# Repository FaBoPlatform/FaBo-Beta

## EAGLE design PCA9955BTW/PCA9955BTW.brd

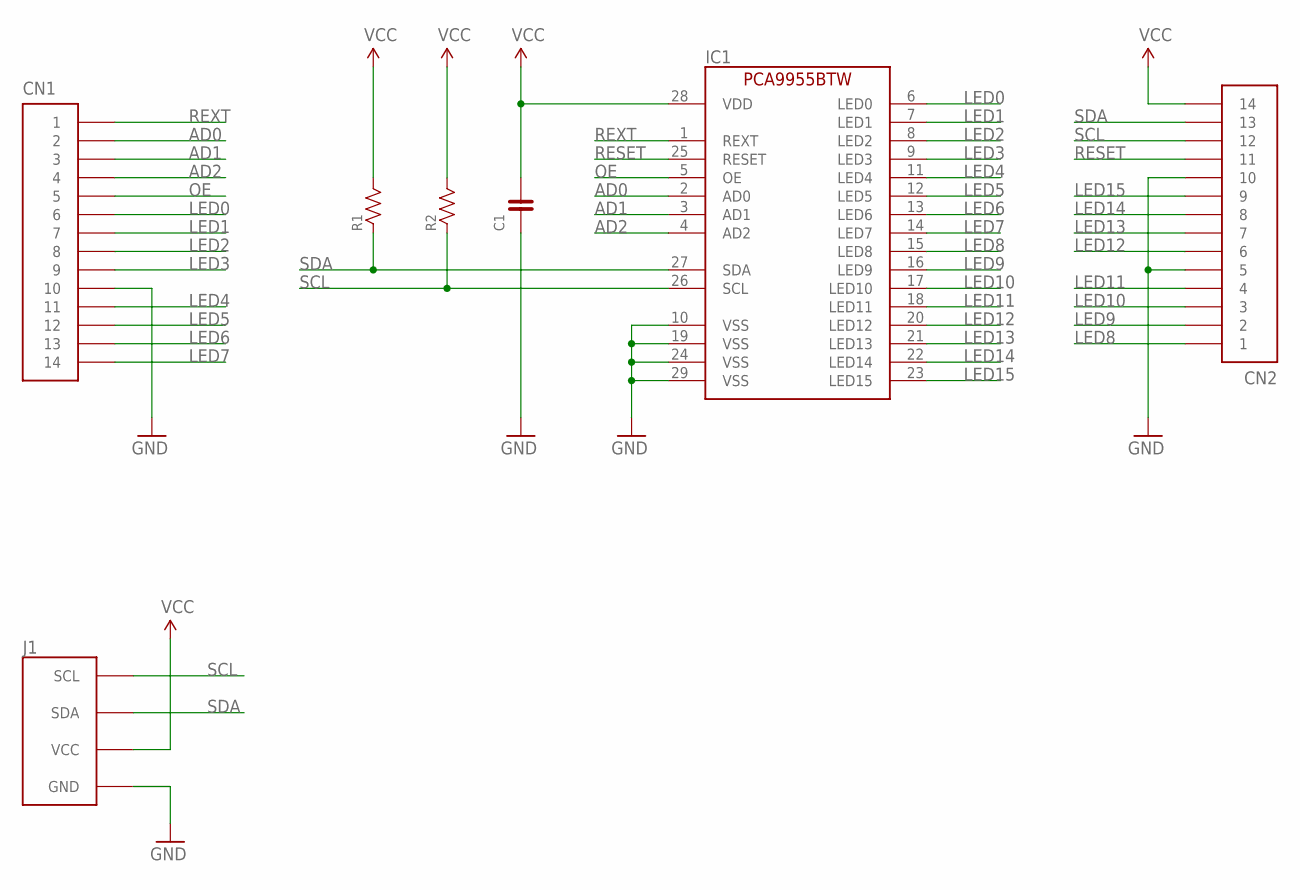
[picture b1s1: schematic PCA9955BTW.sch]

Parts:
C1: CAPACITOR-0603; 0603
CN1, CN2: PIN_HEADER_1X14; PIN_1X14_SNEAKY
IC1: PCA9955BTW; HTSSOP28
J1: FABO_BRICK_I2C-CONNECTOR; FABO_BRICK_I2C_CONNECTOR
R1, R2: RESISTOR-0603; 0603

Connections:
AD0: CN1.2, IC1.2 (AD0)
AD1: CN1.3, IC1.3 (AD1)
AD2: CN1.4, IC1.4 (AD2)
GND: C1.1, CN1.10, CN2.5, CN2.10, IC1.10 (VSS), IC1.19 (VSS), IC1.24 (VSS), IC1.29 (VSS), J1.GND
LED0: CN1.6, IC1.6 (LED0)
LED1: CN1.7, IC1.7 (LED1)
LED2: CN1.8, IC1.8 (LED2)
LED3: CN1.9, IC1.9 (LED3)
LED4: CN1.11, IC1.11 (LED4)
LED5: CN1.12, IC1.12 (LED5)
LED6: CN1.13, IC1.13 (LED6)
LED7: CN1.14, IC1.14 (LED7)
LED8: CN2.1, IC1.15 (LED8)
LED9: CN2.2, IC1.16 (LED9)
LED10: CN2.3, IC1.17 (LED10)
LED11: CN2.4, IC1.18 (LED11)
LED12: CN2.6, IC1.20 (LED12)
LED13: CN2.7, IC1.21 (LED13)
LED14: CN2.8, IC1.22 (LED14)
LED15: CN2.9, IC1.23 (LED15)
OE: CN1.5, IC1.5 (OE)
RESET: CN2.11, IC1.25 (RESET)
REXT: CN1.1, IC1.1 (REXT)
SCL: CN2.12, IC1.26 (SCL), J1.SCL, R2.1
SDA: CN2.13, IC1.27 (SDA), J1.SDA, R1.1
VCC: C1.2, CN2.14, IC1.28 (VDD), J1.VCC, R1.2, R2.2

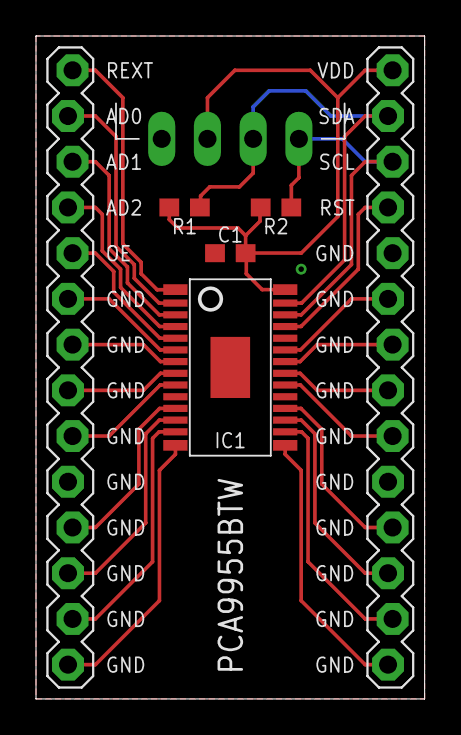
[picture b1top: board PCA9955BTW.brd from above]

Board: 2 copper layers, 21.6 x 36.8 mm, 7 parts (0 on the bottom side), 26 nets.

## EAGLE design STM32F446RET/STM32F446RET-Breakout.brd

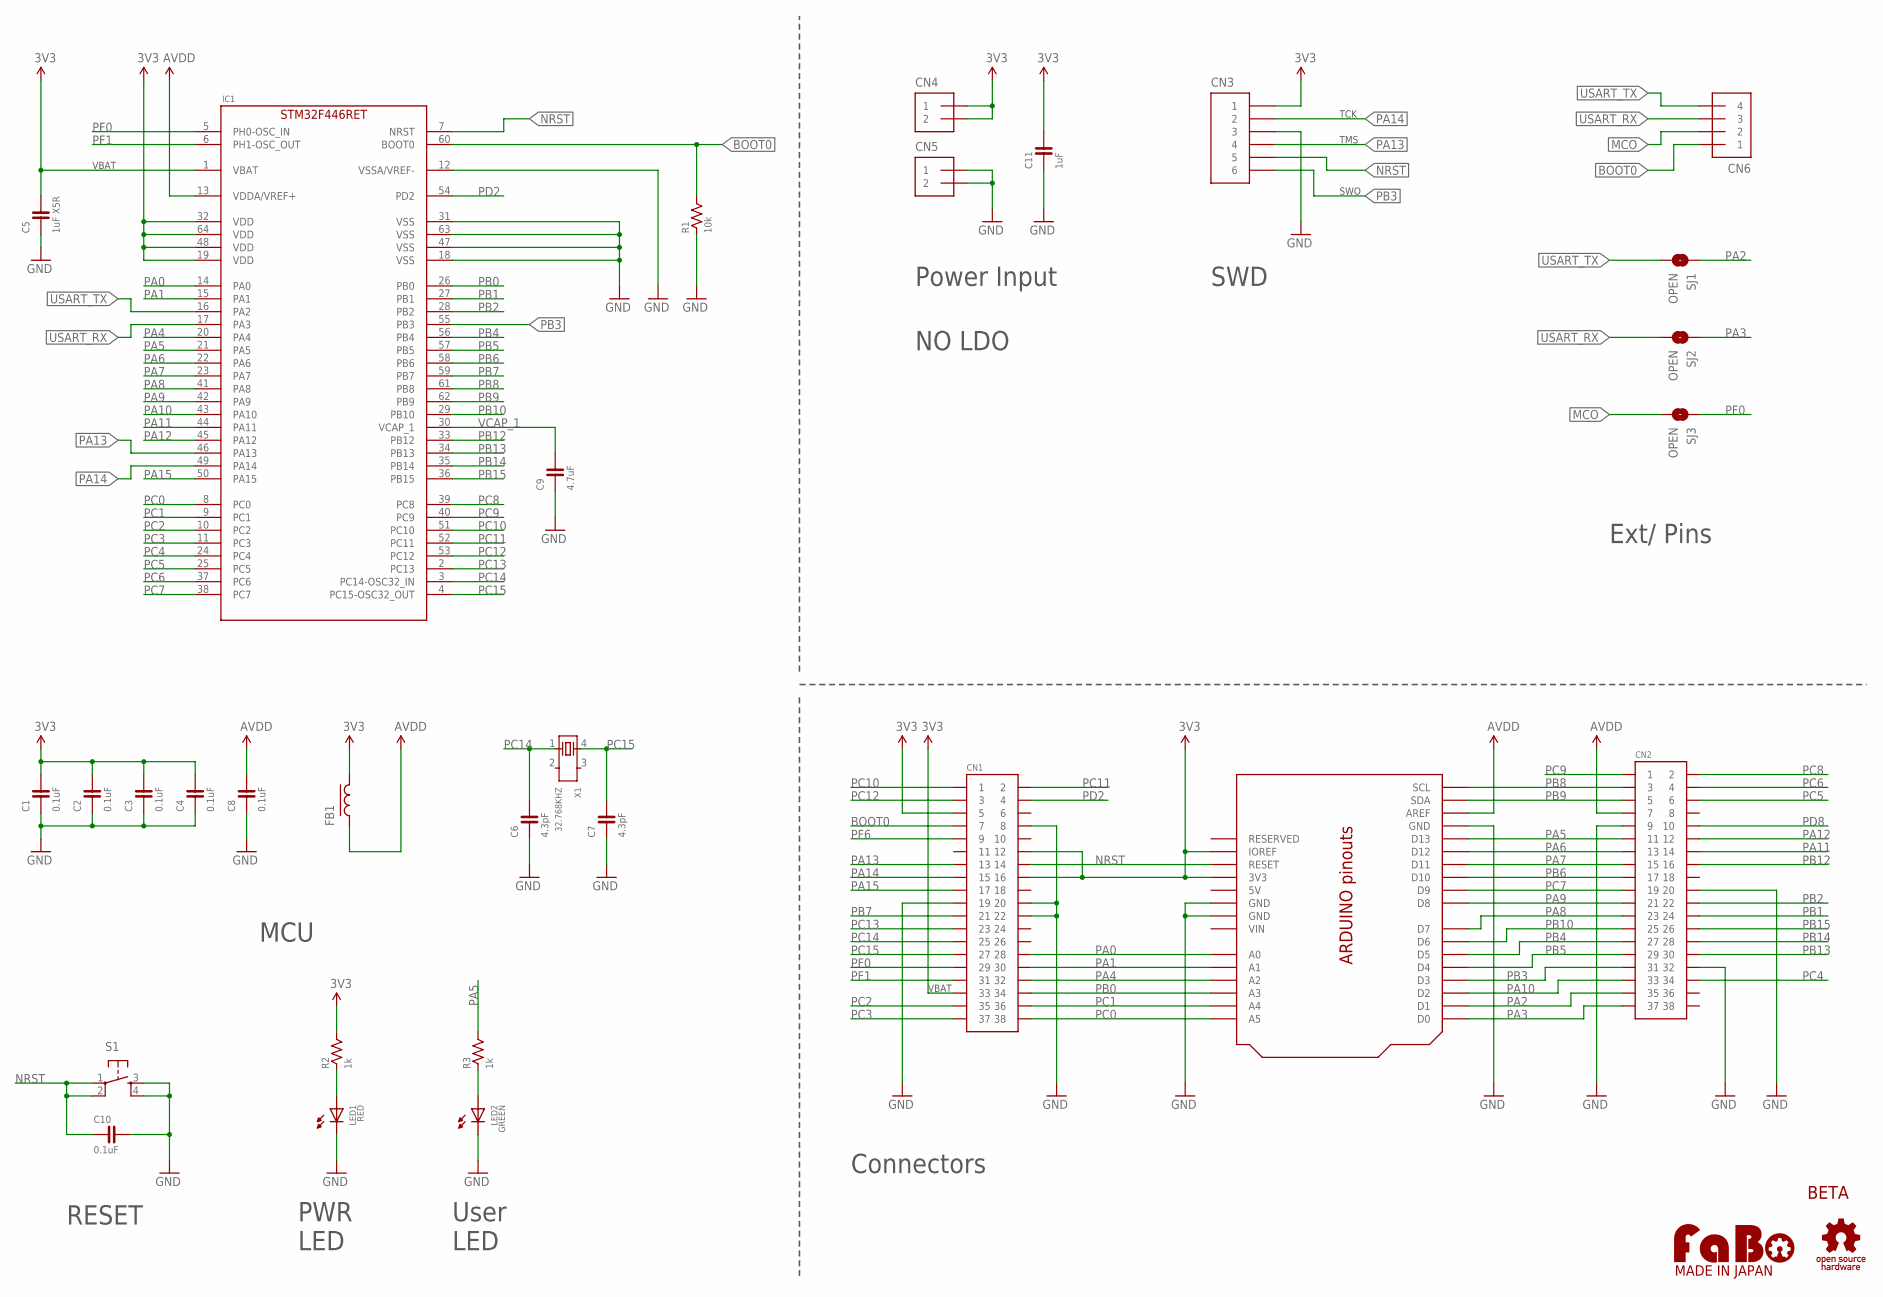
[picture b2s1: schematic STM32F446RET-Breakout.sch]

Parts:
C1, C2, C3, C4, C8, C10: 0.1uF; 0603
C5: 1uF X5R; 0603
C6, C7: 4.3pF; 0603
C9: 4.7uF; 0603
C11: 1uF; 0603
CN1, CN2: PIN_HEADER_2X19; PIN_2X19
CN3: PIN_HEADER_1X6; PIN_1X6
CN4, CN5: PIN_HEADER_1X2; PIN_1X2_LONG
CN6: PIN_HEADER_1X4; PIN_1X4_SNEAKY
FB1: FERRITEBEADS; EIA0603
IC1: STM32F446RET; LQFP-64
LED1: RED; 0603
LED2: GREEN; 0603
R1: 10k; 0603
R2, R3: 1k; 0603
S1: TACT-SWITCH-6MM; DTS_6_V
SJ1, SJ2, SJ3: OPEN; SMD-JUMPER-2-OPEN
U1: ARDUINO_UNO_R3_SHIELD-NUCLEO; NUCLEO
U$2: LOGO_FABO-M; LOGO_FABO_MS
U$3: LOGO_OSHW-M_BOTTOM; LOGO_OSHW_M_BOTTOM
X1: 32.768KHZ; ABRACON-ABS25-32.768KHZ

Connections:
3V3: C1.2, C2.2, C3.2, C4.2, C5.2, C11.2, CN1.5, CN1.12, CN1.16, CN1.33, CN3.1, CN4.1, CN4.2, FB1.2, IC1.1 (VBAT), IC1.19 (VDD), IC1.32 (VDD), IC1.48 (VDD), IC1.64 (VDD), R2.2, U1.3V3, U1.IOREF
5V: U1.5V
AVDD: C8.2, CN2.7, FB1.1, IC1.13 (VDDA/VREF+), U1.AREF
BOOT0: CN1.7, CN6.1, IC1.60 (BOOT0), R1.2
GND: C1.1, C2.1, C3.1, C4.1, C5.1, C6.1, C7.1, C8.1, C9.1, C10.2, C11.1, CN1.8, CN1.19, CN1.20, CN1.22, CN2.9, CN2.20, CN2.32, CN3.3, CN5.1, CN5.2, IC1.12 (VSSA/VREF-), IC1.18 (VSS), IC1.31 (VSS), IC1.47 (VSS), IC1.63 (VSS), LED1.CATHODE, LED2.CATHODE, R1.1, S1.3, S1.4, U1.GND1 (GND), U1.GND2 (GND), U1.GND3 (GND)
MCO: CN6.2, SJ3.2
NRST: C10.1, CN1.14, CN3.5, IC1.7 (NRST), S1.1, S1.2, U1.RESET
PA0: CN1.28, IC1.14 (PA0), U1.A0
PA1: CN1.30, IC1.15 (PA1), U1.A1
PA2: CN2.35, SJ1.1, U1.D1
PA3: CN2.37, SJ2.1, U1.D0
PA4: CN1.32, IC1.20 (PA4), U1.A2
PA5: CN2.11, IC1.21 (PA5), R3.2, U1.D13
PA6: CN2.13, IC1.22 (PA6), U1.D12
PA7: CN2.15, IC1.23 (PA7), U1.D11
PA8: CN2.23, IC1.41 (PA8), U1.D7
PA9: CN2.21, IC1.42 (PA9), U1.D8
PA10: CN2.33, IC1.43 (PA10), U1.D2
PA11: CN2.14, IC1.44 (PA11)
PA12: CN2.12, IC1.45 (PA12)
PA13: CN1.13, CN3.4, IC1.46 (PA13)
PA14: CN1.15, CN3.2, IC1.49 (PA14)
PA15: CN1.17, IC1.50 (PA15)
PB0: CN1.34, IC1.26 (PB0), U1.A3
PB1: CN2.24, IC1.27 (PB1)
PB2: CN2.22, IC1.28 (PB2)
PB3: CN2.31, CN3.6, IC1.55 (PB3), U1.D3
PB4: CN2.27, IC1.56 (PB4), U1.D5
PB5: CN2.29, IC1.57 (PB5), U1.D4
PB6: CN2.17, IC1.58 (PB6), U1.D10
PB7: CN1.21, IC1.59 (PB7)
PB8: CN2.3, IC1.61 (PB8), U1.SCL
PB9: CN2.5, IC1.62 (PB9), U1.SDA
PB10: CN2.25, IC1.29 (PB10), U1.D6
PB12: CN2.16, IC1.33 (PB12)
PB13: CN2.30, IC1.34 (PB13)
PB14: CN2.28, IC1.35 (PB14)
PB15: CN2.26, IC1.36 (PB15)
PC0: CN1.38, IC1.8 (PC0), U1.A5
PC1: CN1.36, IC1.9 (PC1), U1.A4
PC2: CN1.35, IC1.10 (PC2)
PC3: CN1.37, IC1.11 (PC3)
PC4: CN2.34, IC1.24 (PC4)
PC5: CN2.6, IC1.25 (PC5)
PC6: CN2.4, IC1.37 (PC6)
PC7: CN2.19, IC1.38 (PC7), U1.D9
PC8: CN2.2, IC1.39 (PC8)
PC9: CN2.1, IC1.40 (PC9)
PC10: CN1.1, IC1.51 (PC10)
PC11: CN1.2, IC1.52 (PC11)
PC12: CN1.3, IC1.53 (PC12)
PC13: CN1.23, IC1.2 (PC13)
PC14: C6.2, CN1.25, IC1.3 (PC14-OSC32_IN), X1.1
PC15: C7.2, CN1.27, IC1.4 (PC15-OSC32_OUT), X1.4
PD2: CN1.4, IC1.54 (PD2)
PD8: CN2.10
PF0: CN1.29, IC1.5 (PH0-OSC_IN), SJ3.1
PF1: CN1.31, IC1.6 (PH1-OSC_OUT)
PF6: CN1.9
PWRLEDA: LED1.ANODE, R2.1
USART_RX: CN6.3, IC1.17 (PA3), SJ2.2
USART_TX: CN6.4, IC1.16 (PA2), SJ1.2
USRLEDA: LED2.ANODE, R3.1
VCAP_1: C9.2, IC1.30 (VCAP_1)
VIN: U1.VIN

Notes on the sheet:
TCK
TMS
SWO
VBAT
Power Input
MCU
Connectors
SWD
Ext/ Pins
BETA
NO LDO
RESET
PWR LED
User LED

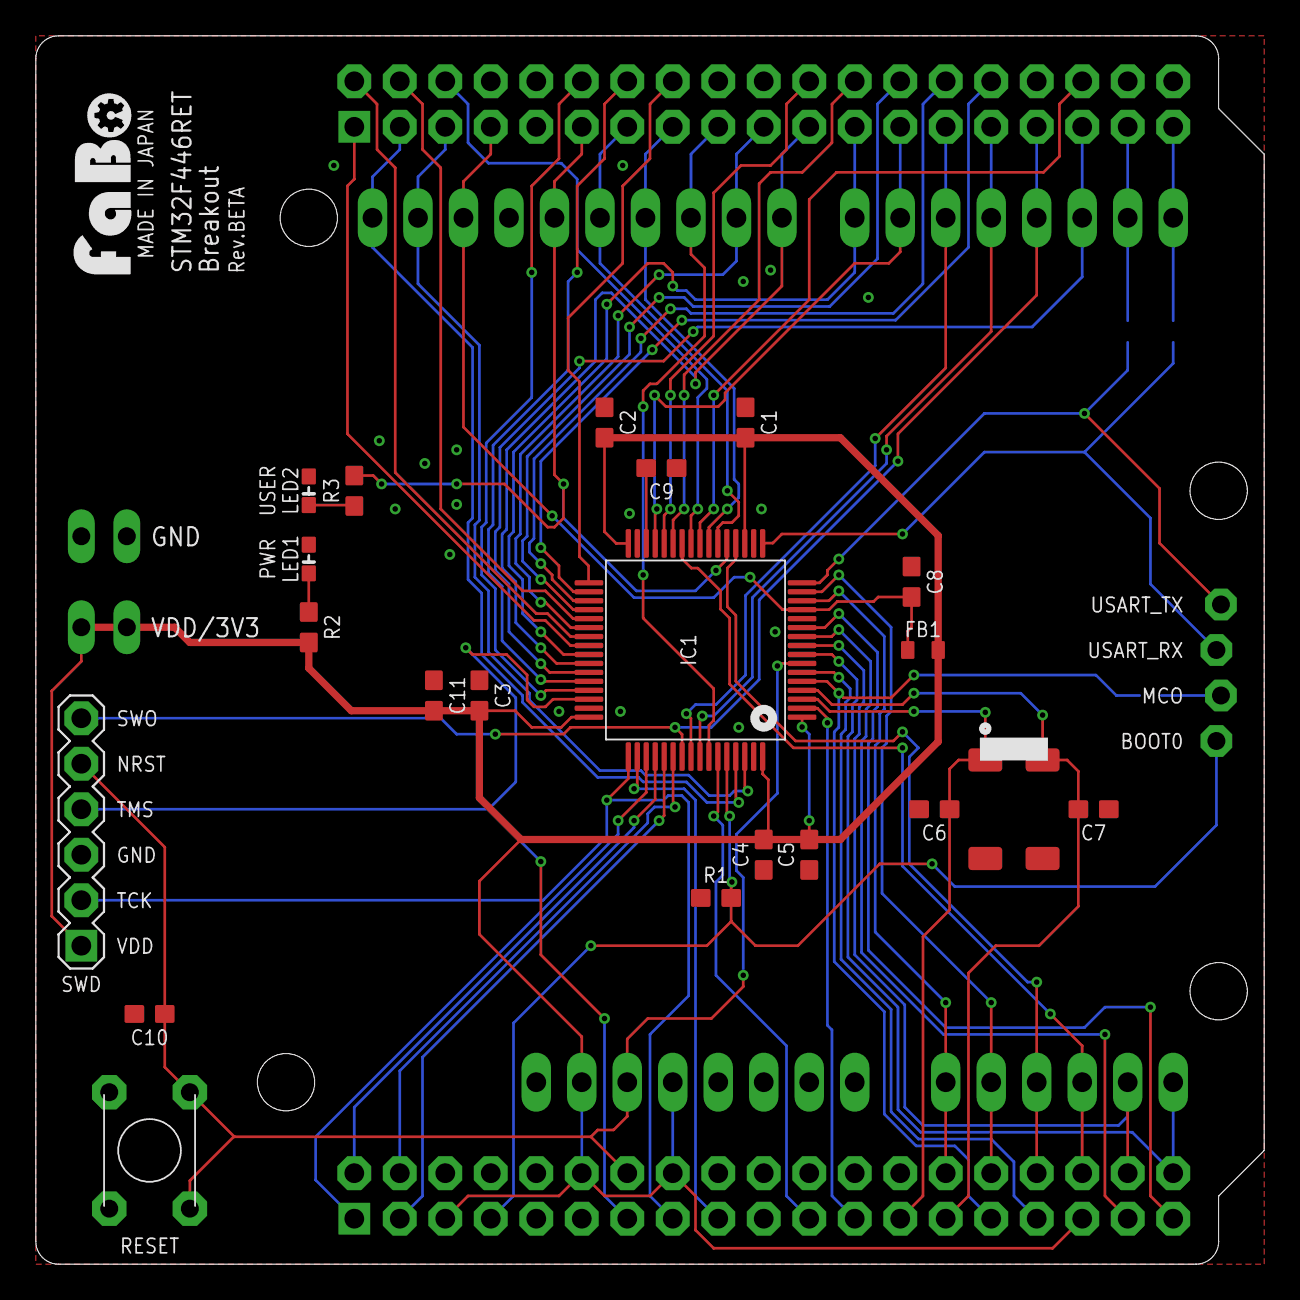
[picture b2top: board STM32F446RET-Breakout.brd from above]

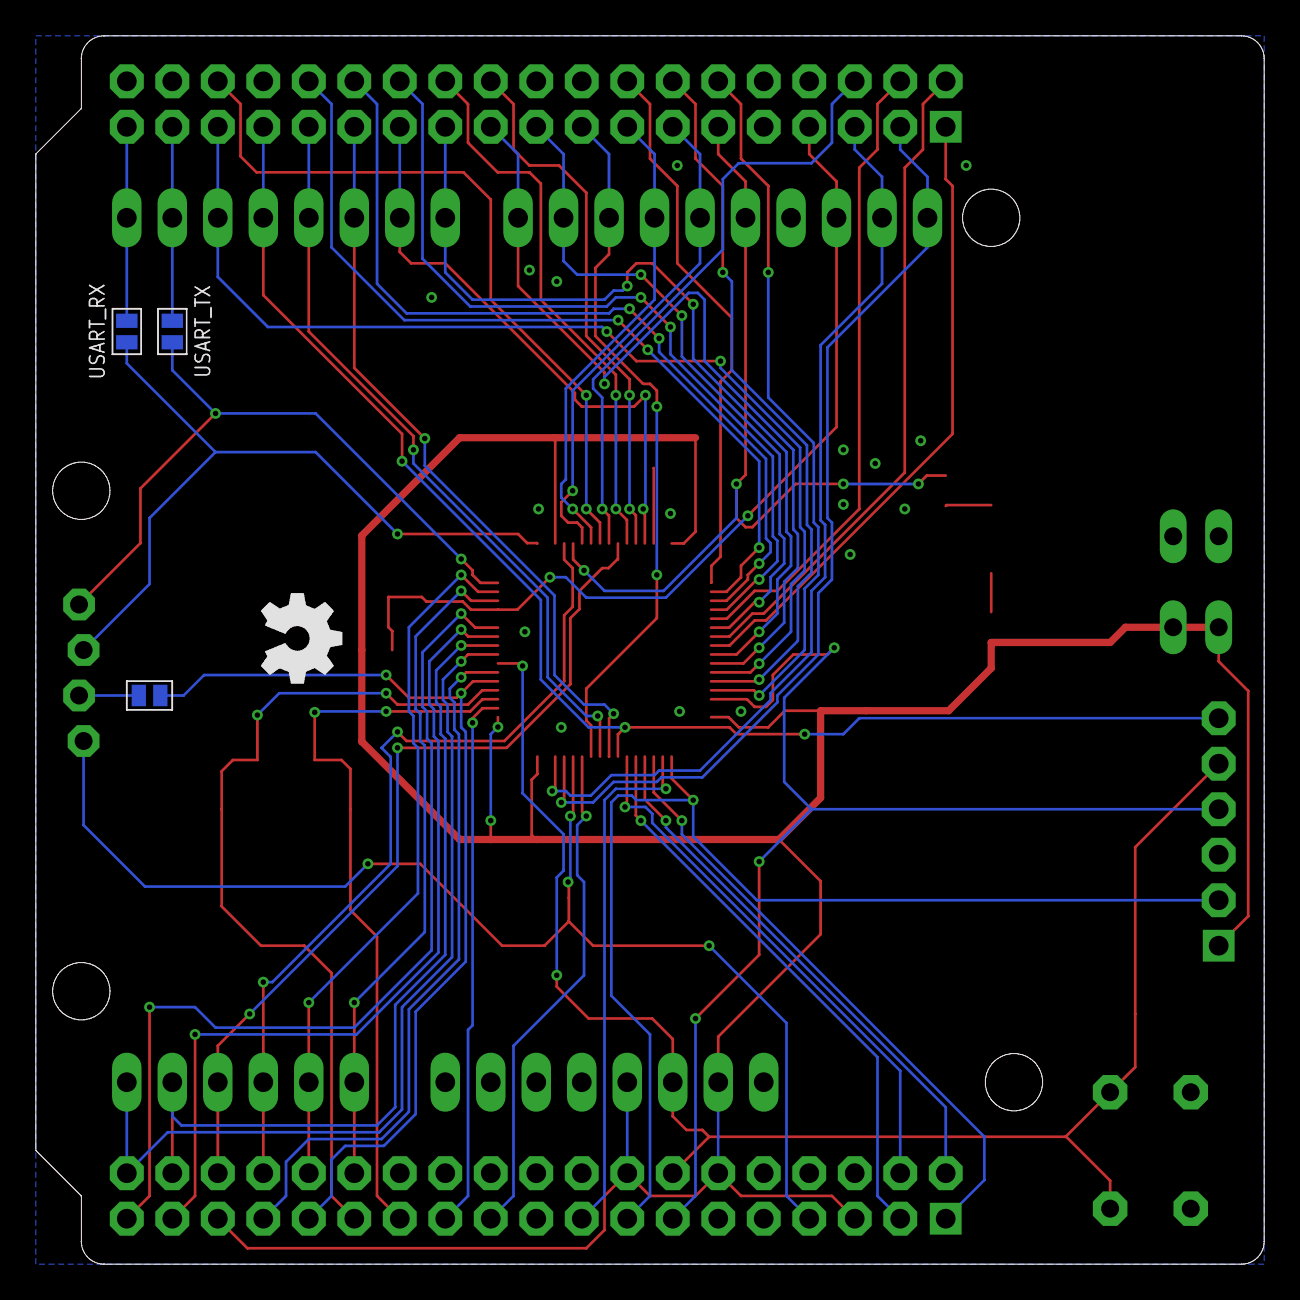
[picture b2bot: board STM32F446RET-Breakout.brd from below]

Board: 2 copper layers, 68.6 x 68.6 mm, 32 parts (3 on the bottom side), 61 nets.

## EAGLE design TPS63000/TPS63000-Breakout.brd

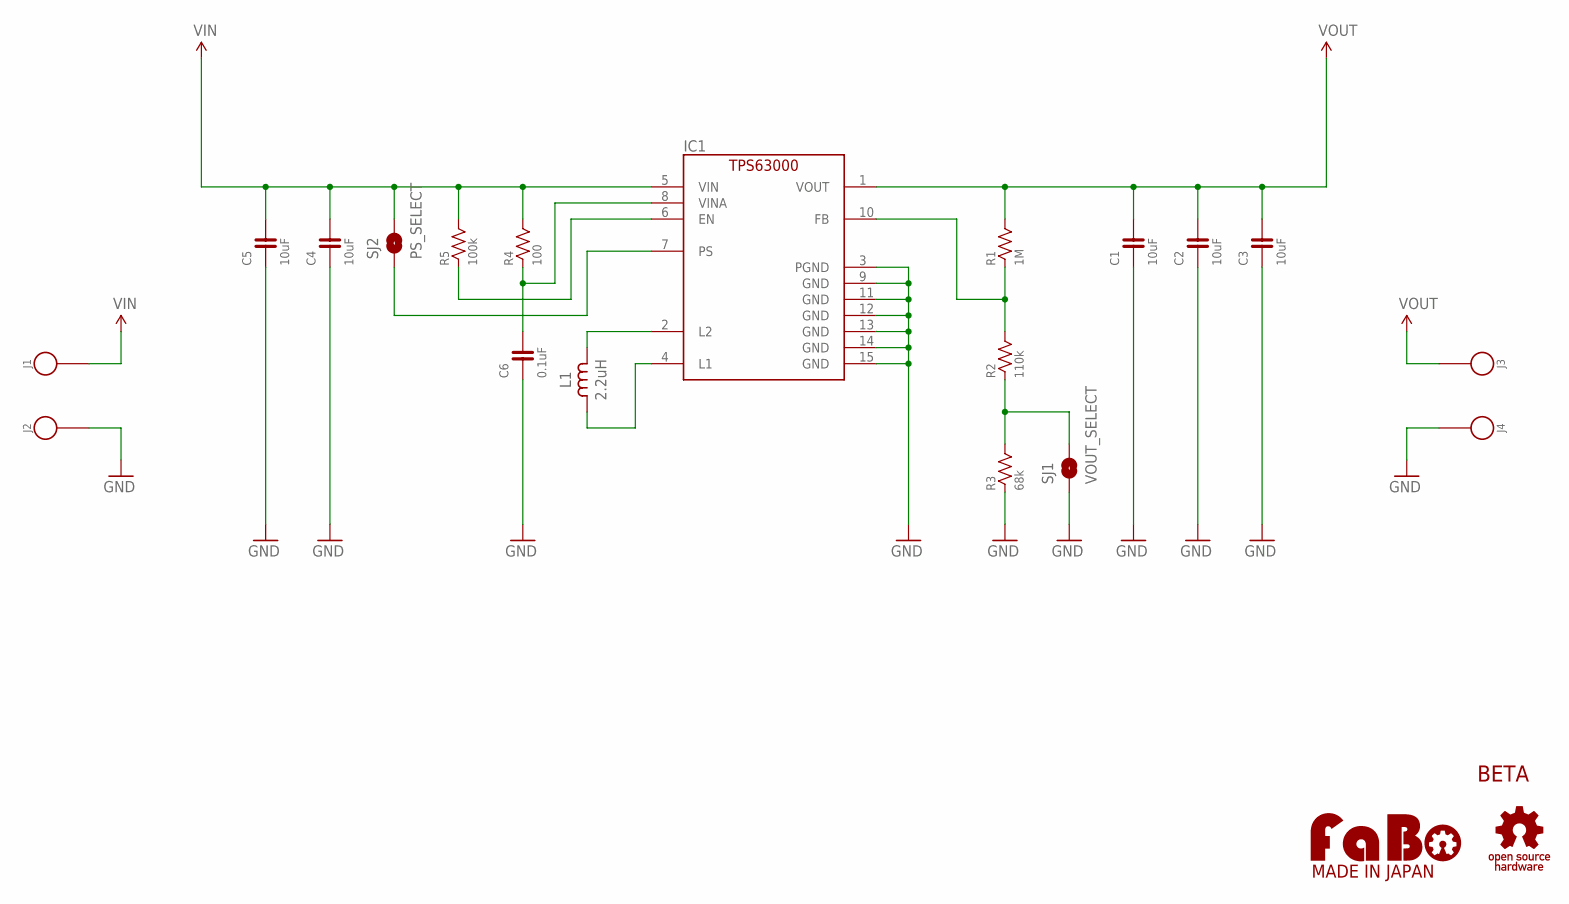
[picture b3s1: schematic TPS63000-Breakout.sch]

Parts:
C1, C2, C3, C4, C5: 10uF; 0603-NARROW
C6: 0.1uF; 0603-NARROW
IC1: TPS63000DRC; VSON-10
J1, J2, J3, J4: PIN_HEADER_1X1_NOLABEL; PIN_1X1_NOLABEL
L1: 2.2uH; LQH3NPN
R1: 1M; 0603-NARROW
R2: 110k; 0603-NARROW
R3: 68k; 0603-NARROW
R4: 100; 0603-NARROW
R5: 100k; 0603-NARROW
SJ1: VOUT_SELECT; SMD-JUMPER-2-SHORT
SJ2: PS_SELECT; SMD-JUMPER-2-SHORT
U$2: LOGO_OSHW-M_BOTTOM; LOGO_OSHW_M_BOTTOM
U$3: LOGO_FABO-M_BOTTOM; LOGO_FABO_MS_BOTTOM

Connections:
EN: IC1.6 (EN), R5.1
FB: IC1.10 (FB), R1.1, R2.2
GND: C1.1, C2.1, C3.1, C4.1, C5.1, C6.1, IC1.3 (PGND), IC1.9 (GND), IC1.11 (GND), IC1.12 (GND), IC1.13 (GND), IC1.14 (GND), IC1.15 (GND), J2.1, J4.1, R3.1, SJ1.2
L1: IC1.4 (L1), L1.1
L2: IC1.2 (L2), L1.2
unnamed: R2.1, R3.2, SJ1.1
PS: IC1.7 (PS), SJ2.2
VIN: C4.2, C5.2, IC1.5 (VIN), J1.1, R4.2, R5.2, SJ2.1
VINA: C6.2, IC1.8 (VINA), R4.1
VOUT: C1.2, C2.2, C3.2, IC1.1 (VOUT), J3.1, R1.2

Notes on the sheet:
BETA

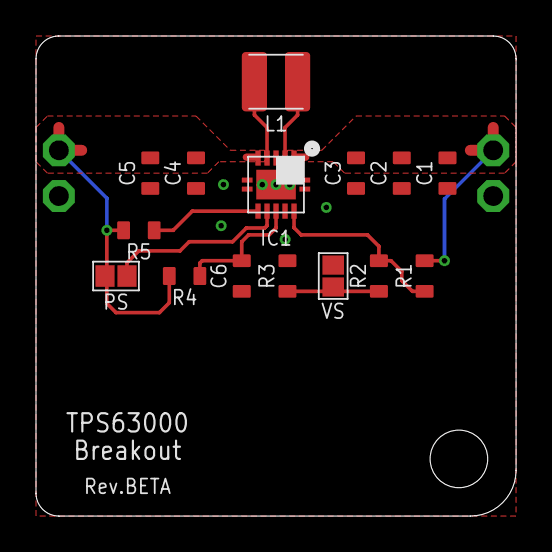
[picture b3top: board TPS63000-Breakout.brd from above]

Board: 2 copper layers, 26.7 x 26.7 mm, 21 parts (0 on the bottom side), 10 nets.

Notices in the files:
parts and their libraries:
FaBo-Capacitor: Released under the Creative Commons Attribution-ShareAlike 4.0 License
https://creativecommons.org/licenses/by-sa/4.0
FaBo-etc: Released under the Creative Commons
